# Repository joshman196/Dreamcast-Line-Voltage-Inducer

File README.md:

# Dreamcast Line Voltage Inducer PCB
PCBs designed to inject 9V into a phone line to play Dreamcast games online. It may be able to do 18V for PAL consoles/modems but this has not been tested. Comes in either a Surface Mount component PCB (tested) or a Through Hole component PCB (untested). It's intended use case is to be hidden inside of a generic RJ11 coupler with the battery snap/barrel jack coming out of a hole that you cut and is tested for this purpose, but should be able to work on the method of cutting the red wire of an RJ11 cable and soldering both sides of the red wire to the PCB.

Please note that while the Through Hole PCB should technically fit inside the case of these generic couplers, it has not actually been tested to see if it will and it is slightly larger than the Surface Mount version. The size was measured and it should fit but it may be very tight. Basically, I really had the surface mount version in mind when this was designed. The Through Hole PCB should work in terms of actually functioning correctly, though.

Yes, I'm aware the Dreamcast Live USB Modem exists and will be the go-to solution for most people. This repository exists if you just want to DIY a line voltage inducer, in case you already have a compatible USB modem or just feel like doing it for fun.

## Parts Required
### Surface Mount PCB
- 1x 0.47uF 50V 0805 Ceramic Capacitor - [I used this one](https://www.digikey.com/en/products/detail/samsung-electro-mechanics/CL21B474KBFNNNG/3894539)
- 1x 360 Ohm 0805 Resistor - [I used this one](https://www.digikey.com/en/products/detail/yageo/RC0805FR-07360RL/727886)
- 1x RJ11 coupler - [I used this one](https://www.amazon.com/dp/B09KX17R23?psc=1&)
- 1x Compatible USB Dial-up Modem (Dell NW147, Lenovo RD02-D400, TRENDnet TFM-561U, or a Zoom 3095)

### Through Hole PCB (Untested)
- 1x 0.47uF 50V Through Hole Capacitor - [This *should* work](https://www.digikey.com/en/products/detail/w%C3%BCrth-elektronik/860010672004/5726903)
- 1x 360 Ohm Through Hole Resistor - [This *should* work](https://www.digikey.com/en/products/detail/stackpole-electronics-inc/CF18JT360R/1741690)
- 1x RJ11 coupler - [I used this one](https://www.amazon.com/dp/B09KX17R23?psc=1&)
- 1x Compatible USB Dial-up Modem (Dell NW147, Lenovo RD02-D400, TRENDnet TFM-561U, or a Zoom 3095)

**And either:**
- 1x 9V Battery Snap (or 2x if you have a PAL Console/Modem) - [Amazon](https://www.amazon.com/Battery-Connector-Plastic-Experiment-Equipment/dp/B08SL9X2YC)
- 9V Batteries - [Amazon](https://www.amazon.com/VONIKO-9V-Batteries-Alkaline-Battery/dp/B07RZ9PMQH/ref=sr_1_9?crid=9077FOBCDWF6&keywords=9v+battery&qid=1704714967&sprefix=9v+battery%2Caps%2C165&sr=8-9)

**OR**

- 1x 2.1mm Barrel Pigtail Cable - [I used this one,](https://www.ledsupply.com/accessories/dc-barrel-plug-pigtail-cable) make sure to select "2.1mm Female"
- 1x 9V Power Supply - [I used this one](https://www.amazon.com/dp/B0BLYS33ZP)

I have tested both a 9V battery and a barrel jack with a 9V power supply but I have not tested the 18V/2x9V batteries method for PAL consoles/modems as I do not own one. Theoretically, it should just work if you wire the batteries according to [this image](https://www.segasaturnshiro.com/wp-content/uploads/2022/06/LVI-PAL-1024x819.jpg). You can also (probably?) use an [18V power supply](https://www.amazon.co.uk/TKDY-Supply-Adapter-Electronics-Positive-Black/dp/B0BRPKVB5P/ref=sr_1_3?crid=2C0WTNA4J7N3&keywords=18v+power+supply&qid=1692327609&sprefix=18v+power+supp%2Caps%2C270&sr=8-3) with the barrel jack method as long as the barrel jack pigtails you buy are rated for at least 18V.

## Install Guide
1. Add the resistor and capacitor to the PCB.
2. Open up the coupler by pulling both sides apart.
3. Cut the red wire inside the RJ11 coupler and strip a bit of the insulation off both sides of it. You may be able to burn off the insulation with a soldering iron if you can't work well with the limited space.
4. Solder both ends of the cut red wire each to the "Red" solder pads on the PCB. It shouldn't matter which way they go.
5. Solder the 9V battery snap or barrel jack pigtail to the "+" and "-" solder pads on the PCB. Make sure you solder the red lead of the battery snap/pigtail to the "+" pad and the black lead to the "-" pad.
6. This is probably optional, but I also recommend that you wrap the PCB with kapton tape after soldering everything.
7. Cut a hole in the side of the RJ11 coupler for the battery snap/barrel jack wires to fit through. I used an off-brand X-acto Knife to cut this hole. Close/fit the coupler together after this.
8. Plug the power supply/battery into the inducer, plug your USB modem into a DreamPi (or PC, instructions later in this step), connect the phone lines from the USB Modem into your coupler, and from the other end of the coupler to your Dreamcast, turn on the DreamPi and connect your Dreamcast to the internet! If you don't have a dedicated DreamPi or any kind of Raspberry Pi to set up DreamPi on, you can use [this simple method](https://www.dreamcast-talk.com/forum/viewtopic.php?t=12731) on a PC to get online.

## Board Types/Pictures

### Surface Mount PCB (~10.287mm x ~5.207mm)

### Through Hole PCB (~14.224mm x ~7.112mm)

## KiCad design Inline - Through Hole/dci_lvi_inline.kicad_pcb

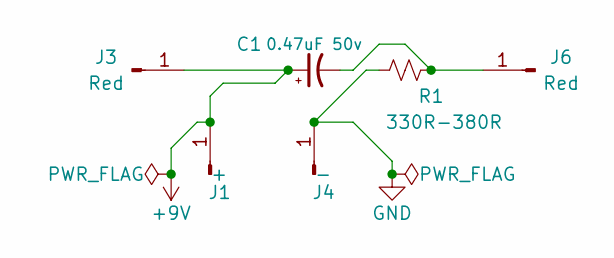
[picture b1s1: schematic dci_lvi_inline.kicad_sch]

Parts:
C1: 0.47uF 50v; CP_Radial_D5.0mm_P2.00mm
J1: +; SolderWirePad_1x01_SMD_1.5x3mm
J3, J6: Red; SolderWirePad_1x01_SMD_1.5x3mm
J4: -; SolderWirePad_1x01_SMD_1.5x3mm
R1: 330R-380R; R_Axial_DIN0204_L3.6mm_D1.6mm_P5.08mm_Horizontal

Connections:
+9V: C1.1, J1.1, J3.1
GND: J4.1, R1.2
unnamed: C1.2, J6.1, R1.1

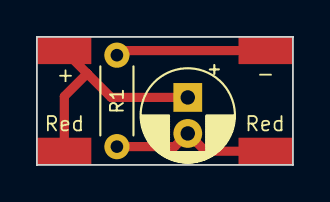
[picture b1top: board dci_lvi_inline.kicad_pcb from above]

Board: 2 copper layers, 14.2 x 7.1 mm, 6 parts (0 on the bottom side), 3 nets.

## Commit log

2023-08-18 Initial file uploads
2023-08-18 retry readme images
    I think the readme images broke when I made the repository public
2023-08-20 attempt to make silkscreen slightly more readable
2023-08-20 reposition silkscreen text
